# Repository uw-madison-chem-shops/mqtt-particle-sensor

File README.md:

# MQTT particle sensor

Designed to work with [mqtt.chem.wisc.edu](https://mqtt.chem.wisc.edu/).

## Repository

This is an open source hardware project licensed under the CERN Open Hardware Licence Version 2 - Permissive.
Please see the LICENSE file for the complete license.

## PCB

This PCB was designed using KiCAD version 7.
Refer to `mqtt_particle_sensor.pdf` for schematic.
PCB images generated with [tracespace](https://github.com/tracespace/tracespace) follow.

## Bill of Materials

| reference      | value         | manufacturer | part number       | price | vendors |
| :------------- | :------------ | :----------- | :---------------- | :---- | :------ |
| C1             | 1u            | Multicomp    | MC1206B105K500CT  | $0.10 | [Newark](https://www.newark.com/multicomp-pro/mc1206b105k500ct/ceramic-capacitor-1uf-50v-x7r/dp/06R4217?ost=mc1206b105k500ct)        |
| C2             | 1u            |  Multicomp   | MC1206B105K500CT  | $0.10 | [Newark](https://www.newark.com/multicomp-pro/mc1206b105k500ct/ceramic-capacitor-1uf-50v-x7r/dp/06R4217?ost=mc1206b105k500ct)        |
| C3             | 100u          | Illinois Capacitor|  107KXM025M| $0.25| [Newark](https://www.newark.com/cornell-dubilier/107kxm025m/aluminum-electrolytic-capacitor/dp/69K8200?ost=107kxm025m)        |
| C4             | 10u           |  Yageo       | CC1206KKX7R8BB106 | $0.25      | [Newark](https://www.newark.com/yageo/cc1206kkx7r8bb106/cap-10uf-25v-mlcc-1206-rohs-compliant/dp/26AK2052?st=cc1206kkx7r8bb106)      |
| C5             | 22u           | Murata Electronics| GRM31CC71C226ME11L| $0.75 | [Newark](https://www.newark.com/murata/grm31cc71c226me11l/cap-22uf-16v-mlcc-1206-rohs-compliant/dp/64AJ4421?ost=grm31cc71c226me11l)         |
| R1             | 470k          | 1206 1/4 1%  |                   |       |         |
| R2             | 1M            | 1206 1/4 1%  |                   |       |         |
| R3             | 1M            | 1206 1/4 1%  |                   |       |         |
| R4             | 4.7k          | 1206 1/4 1%  |                   |       |         |
| R5             | 4.7k          | 1206 1/4 1%  |                   |       |         |
| R6             | 1k            | 1206 1/4 1%  |                   |       |         |
| R7             | 1k            | 1206 1/4 1%  |                   |       |         |
| R8             | 4.7k          | 1206 1/4 1%  |                   |       |         |
| R9             | 4.7k          | 1206 1/4 1%  |                   |       |         |
| A1             | ESP8266 HUZZAH BREAKOUT BOARD | Adafruit | 2471 |  $10.00 | [Newark](https://www.newark.com/adafruit/2471/adafruit-huzzah-esp8266-breakout/dp/98Y0121?ost=esp8266+huzzah+breakout+board&cfm=true)        |
| U1             | Auto Reset Timer | Nexperia  | HEF4060BT,653 | $0.50      |[Newark](https://www.newark.com/nexperia/hef4060bt-653/ic-4000-locmos-smd-4060-soic16/dp/25M9620?st=hef4060bt,653)        |
| U2             | ATtiny85      | Microchip Technology| ATTINY85-20PU| $3.00       | [Newark](https://www.newark.com/microchip/attiny85-20pu/microcontroller-mcu-8-bit-attiny/dp/68T3808?ost=attiny85-20pu)|
| U2             | 8pin Dip Socket | Millmax | 110-93-308-41-001000| $1.00 | [Newark](https://www.newark.com/mill-max/110-93-308-41-001000/dip-socket-8-position-through/dp/17C2295?ost=110-93-308-41-001000)|
| U3             | HPM Particle Sensor | Honeywell  | 	HPMA115S0-XXX| $63.75      |  [Newark](https://www.newark.com/honeywell/hpma115s0-xxx/particle-sensor-laser-uart-5v/dp/24AC9030?st=hpm%20particle%20sensor)       |
| U3             | Header Connector    | Molex      | 53047-0810    | $0.14 | [Newark](https://www.newark.com/molex/53047-0810/connector-header-8pos-1row-1-25mm/dp/98K9826?st=53047-0810)|
| U3             | 8pin ribbon cable   | Molex      | 151340801 | $10.06 | [Newark](https://www.newark.com/molex/15134-0801/cable-assy-8pos-rcpt-rcpt-100mm/dp/01AC7007?ost=151340801)|
| D1             | LED (red)          |  Lite-On Inc. | LTST-C230KRKT | $0.25      | [Digikey](https://www.digikey.com/en/products/detail/liteon/LTST-C230KRKT/386857?s=N4IgTCBcDaIDIBUDKCC0BhMBmADAaQCU8EQBdAXyA)        |
| D2             | LED (green)         |  Lite-On Inc | LTST-C150KGKT| $0.25      | [Digikey](https://www.digikey.com/en/products/detail/liteon/LTST-C150KGKT/365085?s=N4IgTCBcDaIDIBUDKCC0BhAjAVgAwGkBxfBEAXQF8g)        |
| PS1            | Power         | CUI   | VXO7805-500-M-TR | $3.00      |[Newark](https://www.newark.com/cui/vxo7805-500-m-tr/dc-dc-converter-fixed-5v-rohs/dp/13AJ1536?ost=vxo7805-500-m-tr)        |
| J2             | Barrel Jack   |CUI |  PJ-002A  | $1.00      | [Digikey](https://www.digikey.com/en/products/detail/cui-devices/PJ-002A/96962)       |
| Q1             | 2N7000          | Diodes Inc.  | 2N7002K-7  |$0.25     |[Newark](https://www.newark.com/diodes-inc/2n7002k-7/mosfet-n-channel-60-v-800ma-sot/dp/25R5681?st=2n7002k-7)         |
| Q2             | 2N7000          | Diodes Inc.  | 2N7002K-7  |$0.25     |[Newark](https://www.newark.com/diodes-inc/2n7002k-7/mosfet-n-channel-60-v-800ma-sot/dp/25R5681?st=2n7002k-7)         |

## Firmware

This project uses [micropython](https://micropython.org/), specifically [microhomie](https://github.com/microhomie/microhomie).
Refer to the "firmware" directory in this repository for detailed instructions.

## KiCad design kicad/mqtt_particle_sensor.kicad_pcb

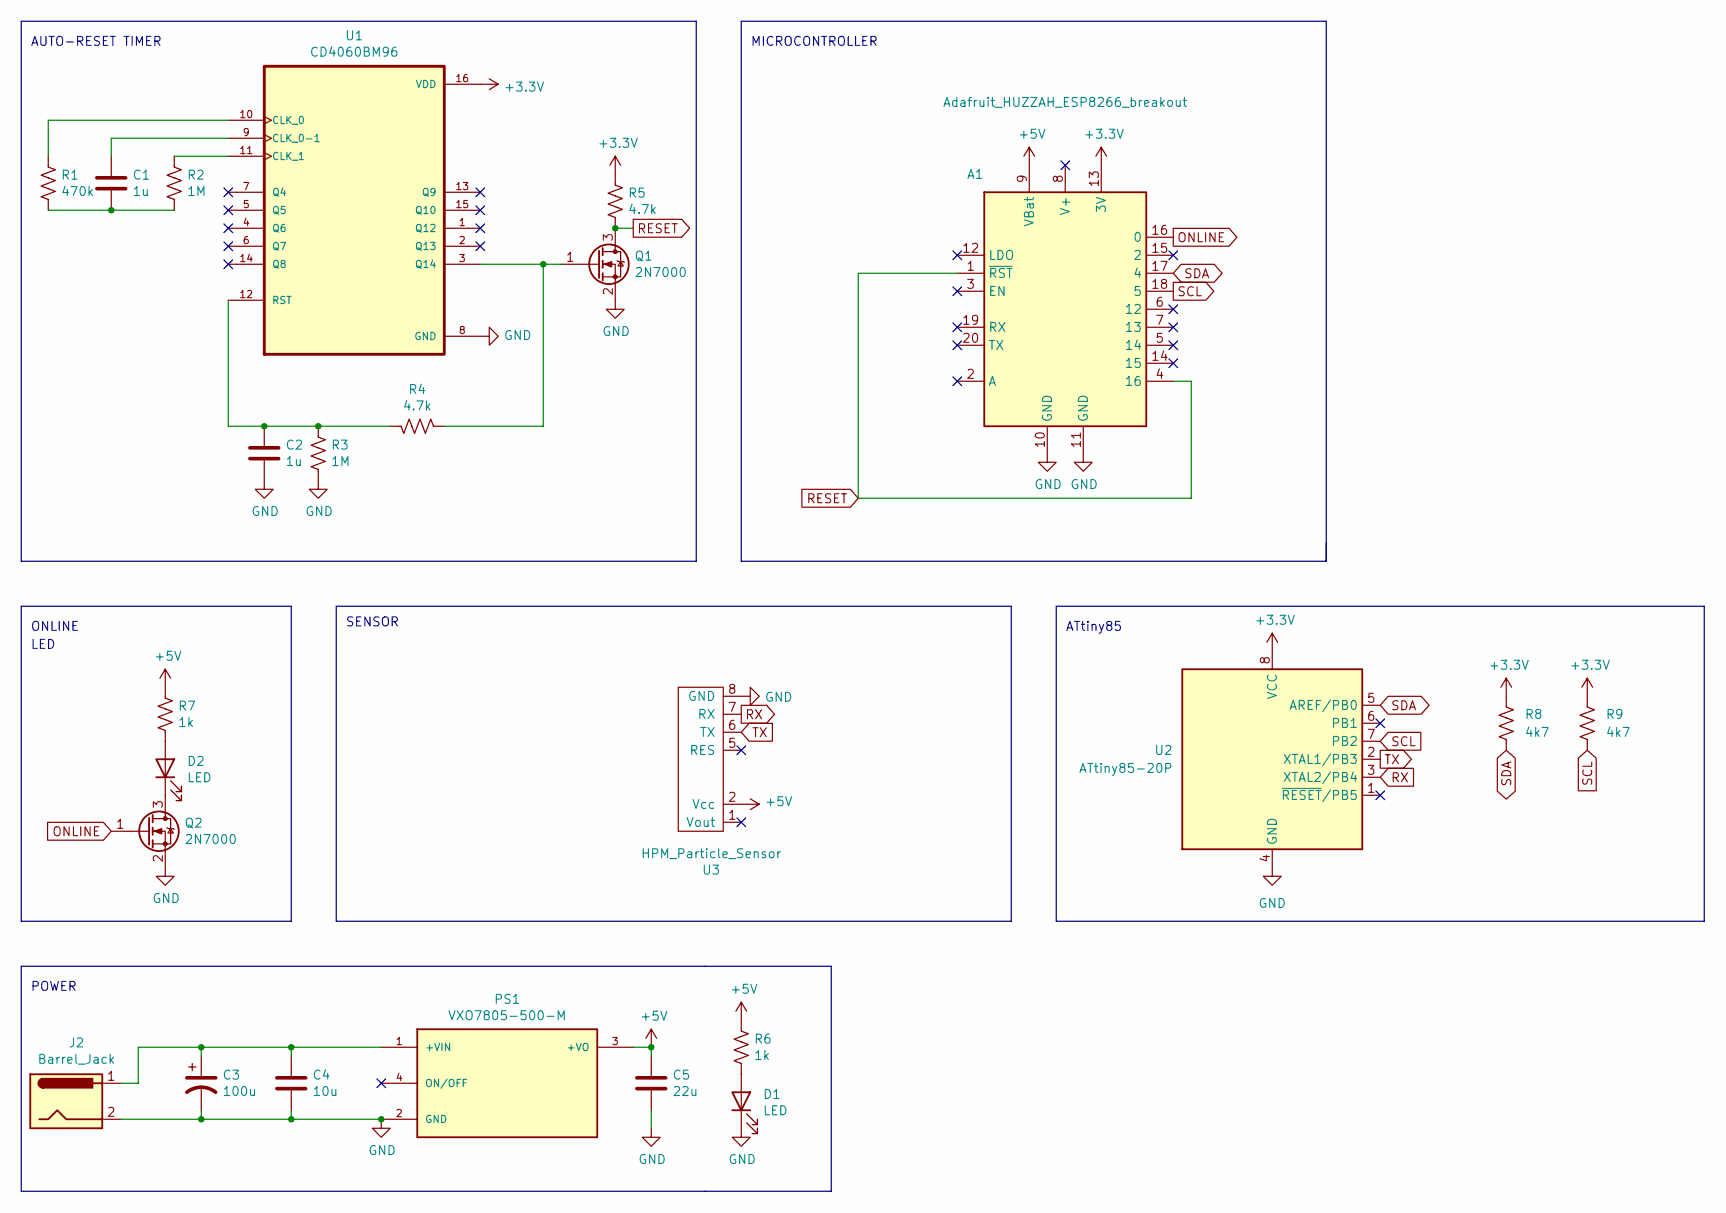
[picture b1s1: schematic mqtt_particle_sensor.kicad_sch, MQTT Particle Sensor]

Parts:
A1: Adafruit_HUZZAH_ESP8266_breakout
C1, C2: 1u; C_1206_3216Metric_Pad1.33x1.80mm_HandSolder
C3: 100u; CP_Radial_Tantal_D7.0mm_P2.50mm
C4: 10u; C_1206_3216Metric_Pad1.33x1.80mm_HandSolder
C5: 22u; C_1206_3216Metric_Pad1.33x1.80mm_HandSolder
D1, D2: LED; LED_1206_3216Metric_Pad1.42x1.75mm_HandSolder
J2: Barrel_Jack; BarrelJack_Horizontal
PS1: VXO7805-500-M; CONV_VXO7805-500-M
Q1, Q2: 2N7000; SOT-23_Handsoldering
R1: 470k; R_1206_3216Metric_Pad1.30x1.75mm_HandSolder
R2, R3: 1M; R_1206_3216Metric_Pad1.30x1.75mm_HandSolder
R4, R5: 4.7k; R_1206_3216Metric_Pad1.30x1.75mm_HandSolder
R6, R7: 1k; R_1206_3216Metric_Pad1.30x1.75mm_HandSolder
R8, R9: 4k7; R_1206_3216Metric_Pad1.30x1.75mm_HandSolder
U1: CD4060BM96; SOIC-16_3.9x9.9mm_P1.27mm
U2: ATtiny85-20P; DIP-8_W7.62mm
U3: HPM_Particle_Sensor; honewell-hpm

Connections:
+3V3: A1.13 (3V), R5.1, R8.1, R9.1, U1.16 (VDD), U2.8 (VCC)
+5V: A1.9 (VBat), C5.1, PS1.3 (+VO), R6.1, R7.1, U3.2 (Vcc)
GND: A1.10 (GND), A1.11 (GND), C2.2, C3.2, C4.2, C5.2, D1.1 (K), J2.2, PS1.2 (GND), Q1.2 (S), Q2.2 (S), R3.2, U1.8 (GND), U2.4 (GND), U3.8 (GND)
unnamed: C1.2, R1.1, R2.1
unnamed: D1.2 (A), R6.2
unnamed: D2.2 (A), R7.2
unnamed: D2.1 (K), Q2.3 (D)
unnamed: C3.1, C4.1, J2.1, PS1.1 (+VIN)
unnamed: Q1.1 (G), R4.1, U1.3 (Q14)
unnamed: R1.2, U1.10 (CLK_0)
unnamed: C1.1, U1.9 (CLK_0-1)
unnamed: R2.2, U1.11 (CLK_1)
unnamed: C2.1, R3.1, R4.2, U1.12 (RST)
ONLINE: A1.16 (0), Q2.1 (G)
RESET: A1.1 (~RST), A1.4 (16), Q1.3 (D), R5.2
RX: U2.3 (XTAL2/PB4), U3.7 (RX)
SCL: A1.18 (5), R9.2, U2.7 (PB2)
SDA: A1.17 (4), R8.2, U2.5 (AREF/PB0)
TX: U2.2 (XTAL1/PB3), U3.6 (TX)

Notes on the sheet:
AUTO-RESET TIMER
MICROCONTROLLER
LED
POWER
ATtiny85
ONLINE
SENSOR

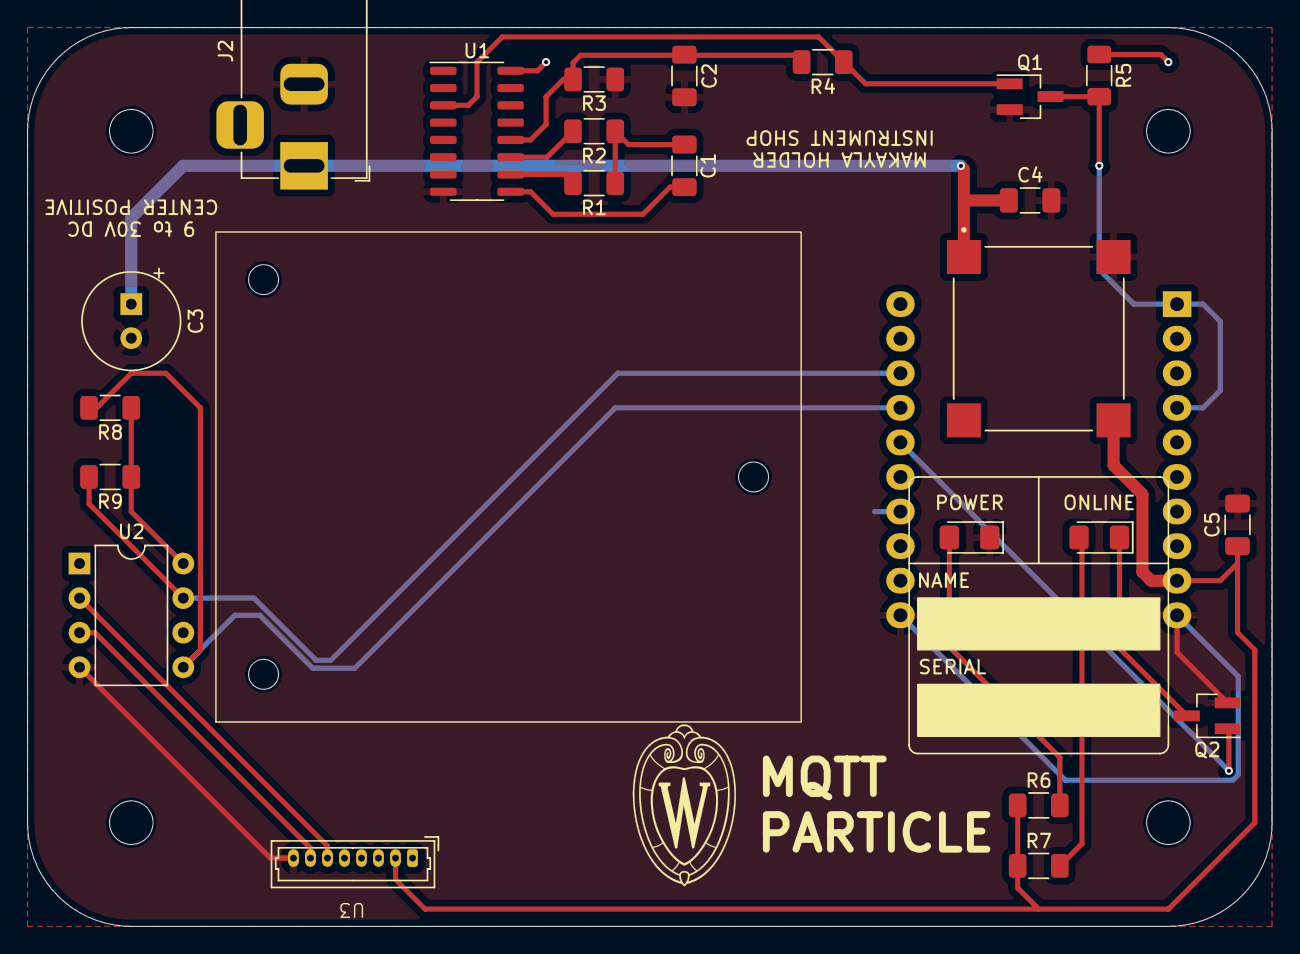
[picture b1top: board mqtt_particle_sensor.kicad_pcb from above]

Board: 2 copper layers, 91.4 x 66.0 mm, 24 parts (1 on the bottom side), 19 nets.

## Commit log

2021-07-09 Added all current files for mqtt-particle-sensor
2021-07-09 rm explicit settings
2023-04-06 revB
2023-06-12 checkpoint
2023-07-14 tiny firmware
2023-08-07 revC
2023-09-18 Update README.md
    Added Bill of Materials for revision C of the mqtt particle sensor
2023-09-18 Update README.md
    Updated Bill of Materials to include more parts that were not accounted for
2023-10-30 hpm i2c
2023-12-06 firmware reset attiny
